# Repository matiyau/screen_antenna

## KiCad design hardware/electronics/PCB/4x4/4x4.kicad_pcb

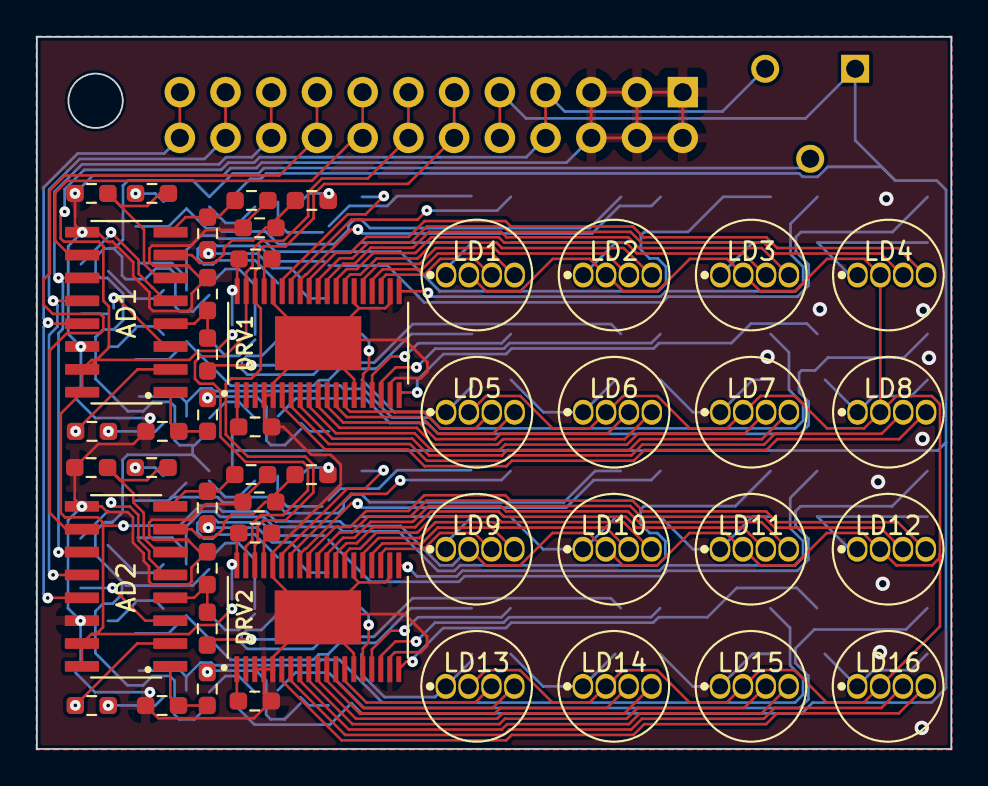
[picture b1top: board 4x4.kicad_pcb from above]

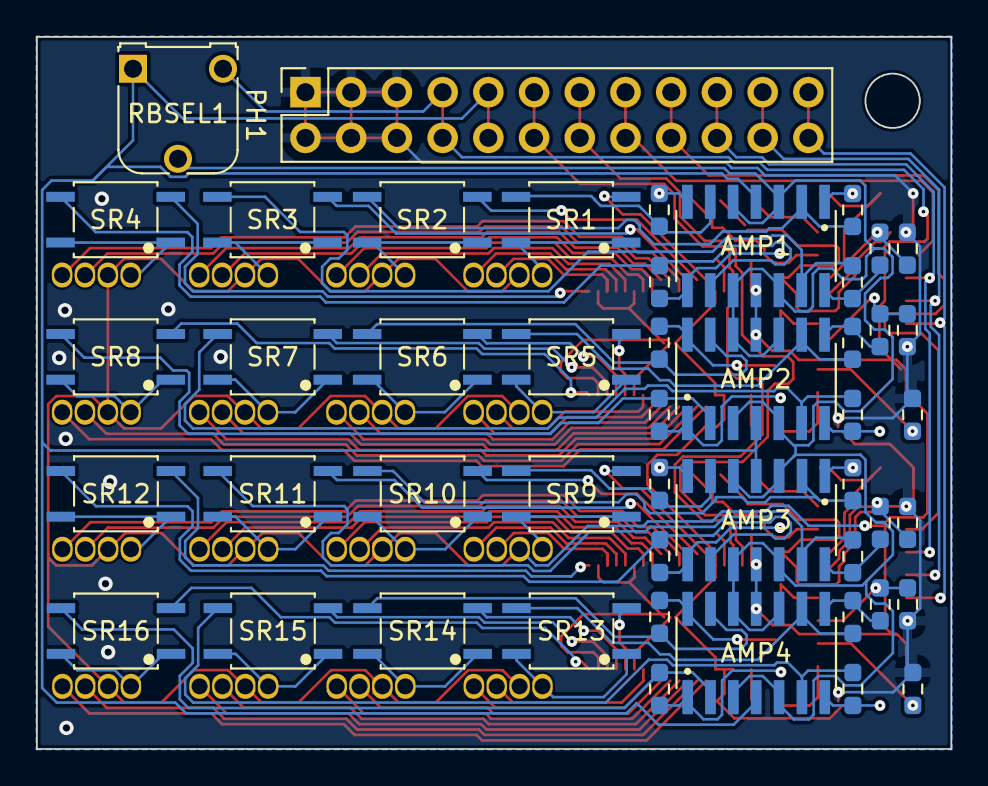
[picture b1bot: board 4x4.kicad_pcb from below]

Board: 2 copper layers, 50.8 x 39.6 mm, 94 parts (48 on the bottom side), 127 nets.

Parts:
AD1, AD2: MCP3008-I/P-DIP16; footprints_smd
AMP1, AMP2, AMP3, AMP4: MCP619-I/SL; footprints
DIV1, DIV2, DIV3, DIV4, DIV5, DIV6, DIV7, DIV8, DIV9, DIV10, DIV11, DIV12, DIV13, DIV14, DIV15, DIV16, DIV17, DIV18, DIV19, DIV20, DIV21, DIV22, DIV23, DIV24, DIV25, DIV26, DIV27, DIV28, DIV29, DIV30, DIV31, DIV32: 2K; Resistor - SMD - 1608Metric
DRV1, DRV2: PCA9956BTWY; SOP50P640X110-39N
FDB1, FDB2, FDB3, FDB4, FDB5, FDB6, FDB7, FDB8, FDB9, FDB10, FDB11, FDB12, FDB13, FDB14, FDB15, FDB16: 2M; Resistor - SMD - 1608Metric
ISEL1, ISEL2: 2K; Resistor - SMD - 1608Metric
LD1, LD2, LD3, LD4, LD5, LD6, LD7, LD8, LD9, LD10, LD11, LD12, LD13, LD14, LD15, LD16: WP154A4SEJ3VBDZGC/CA; WP154A4SEJ3VBDZGC&slash_CA
PH1: Conn_02x12_Odd_Even; PinSocket_2x12_P2.54mm_Vertical
PU1, PU2: 10K; Resistor - SMD - 1608Metric
RBSEL1: 100K; Potentiometer_Runtron_RM-065_Vertical
SR1, SR2, SR3, SR4, SR5, SR6, SR7, SR8, SR9, SR10, SR11, SR12, SR13, SR14, SR15, SR16: TLP4176ATP_F; footprints

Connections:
+5V: AD1.15 (VREF), AD1.16 (VDD), AD2.15 (VREF), AD2.16 (VDD), AMP1.11 (VSS), AMP2.11 (VSS), AMP3.11 (VSS), AMP4.11 (VSS), DRV1.38 (VDD), DRV2.38 (VDD), LD1.2 (CA), LD2.2 (CA), LD3.2 (CA), LD4.2 (CA), LD5.2 (CA), LD6.2 (CA), LD7.2 (CA), LD8.2 (CA), LD9.2 (CA), LD10.2 (CA), LD11.2 (CA), LD12.2 (CA), LD13.2 (CA), LD14.2 (CA), LD15.2 (CA), LD16.2 (CA), PH1.7, PH1.8, PU1.1, PU2.1, RBSEL1.3
+9V: AMP1.4 (VDD), AMP2.4 (VDD), AMP3.4 (VDD), AMP4.4 (VDD), PH1.9, PH1.10, RBSEL1.1
/LED 4x2 Bottom/ LDRow_Amps1/Amp_IP_1: AMP3.2 (VINA-), FDB9.2, SR10.3 (Load)
/LED 4x2 Bottom/ LDRow_Amps1/Amp_IP_2: AMP3.6 (VINB-), FDB10.2, SR9.3 (Load)
/LED 4x2 Bottom/ LDRow_Amps1/Amp_IP_3: AMP3.9 (VINC-), FDB11.2, SR12.3 (Load)
/LED 4x2 Bottom/ LDRow_Amps1/Amp_IP_4: AMP3.13 (VIND-), FDB12.2, SR11.3 (Load)
/LED 4x2 Bottom/ LDRow_Amps1/Amp_IP_5: AMP4.2 (VINA-), FDB13.2, SR16.3 (Load)
/LED 4x2 Bottom/ LDRow_Amps1/Amp_IP_6: AMP4.6 (VINB-), FDB14.2, SR15.3 (Load)
/LED 4x2 Bottom/ LDRow_Amps1/Amp_IP_7: AMP4.9 (VINC-), FDB15.2, SR13.3 (Load)
/LED 4x2 Bottom/ LDRow_Amps1/Amp_IP_8: AMP4.13 (VIND-), FDB16.2, SR14.3 (Load)
/LED 4x2 Bottom/ LDRow_Amps1/Amp_OP_1: AMP3.1 (VOUTA), DIV19.2, FDB9.1
/LED 4x2 Bottom/ LDRow_Amps1/Amp_OP_2: AMP3.7 (VOUTB), DIV17.2, FDB10.1
/LED 4x2 Bottom/ LDRow_Amps1/Amp_OP_3: AMP3.8 (VOUTC), DIV23.2, FDB11.1
/LED 4x2 Bottom/ LDRow_Amps1/Amp_OP_4: AMP3.14 (VOUTD), DIV21.2, FDB12.1
/LED 4x2 Bottom/ LDRow_Amps1/Amp_OP_5: AMP4.1 (VOUTA), DIV31.2, FDB13.1
/LED 4x2 Bottom/ LDRow_Amps1/Amp_OP_6: AMP4.7 (VOUTB), DIV29.2, FDB14.1
/LED 4x2 Bottom/ LDRow_Amps1/Amp_OP_7: AMP4.8 (VOUTC), DIV25.2, FDB15.1
/LED 4x2 Bottom/ LDRow_Amps1/Amp_OP_8: AMP4.14 (VOUTD), DIV27.2, FDB16.1
/LED 4x2 Bottom/LD1_B: DRV2.22 (LED13), LD9.3 (B)
/LED 4x2 Bottom/LD1_G: DRV2.23 (LED14), LD9.4 (G)
/LED 4x2 Bottom/LD1_R: LD9.1 (R), SR9.1 (+Ctr), SR9.4 (Load)
/LED 4x2 Bottom/LD2_B: DRV2.24 (LED15), LD10.3 (B)
/LED 4x2 Bottom/LD2_G: DRV2.26 (LED16), LD10.4 (G)
/LED 4x2 Bottom/LD2_R: LD10.1 (R), SR10.1 (+Ctr), SR10.4 (Load)
/LED 4x2 Bottom/LD3_B: DRV2.27 (LED17), LD11.3 (B)
/LED 4x2 Bottom/LD3_G: DRV2.28 (LED18), LD11.4 (G)
/LED 4x2 Bottom/LD3_R: LD11.1 (R), SR11.1 (+Ctr), SR11.4 (Load)
/LED 4x2 Bottom/LD4_B: DRV2.29 (LED19), LD12.3 (B)
/LED 4x2 Bottom/LD4_G: DRV2.30 (LED20), LD12.4 (G)
/LED 4x2 Bottom/LD4_R: LD12.1 (R), SR12.1 (+Ctr), SR12.4 (Load)
/LED 4x2 Bottom/LD5_B: DRV2.13 (LED7), LD13.3 (B)
/LED 4x2 Bottom/LD5_G: DRV2.12 (LED6), LD13.4 (G)
/LED 4x2 Bottom/LD5_R: LD13.1 (R), SR13.1 (+Ctr), SR13.4 (Load)
/LED 4x2 Bottom/LD6_B: DRV2.11 (LED5), LD14.3 (B)
/LED 4x2 Bottom/LD6_G: DRV2.10 (LED4), LD14.4 (G)
/LED 4x2 Bottom/LD6_R: LD14.1 (R), SR14.1 (+Ctr), SR14.4 (Load)
/LED 4x2 Bottom/LD7_B: DRV2.9 (LED3), LD15.3 (B)
/LED 4x2 Bottom/LD7_G: DRV2.8 (LED2), LD15.4 (G)
/LED 4x2 Bottom/LD7_R: LD15.1 (R), SR15.1 (+Ctr), SR15.4 (Load)
/LED 4x2 Bottom/LD8_B: DRV2.7 (LED1), LD16.3 (B)
/LED 4x2 Bottom/LD8_G: DRV2.6 (LED0), LD16.4 (G)
/LED 4x2 Bottom/LD8_R: LD16.1 (R), SR16.1 (+Ctr), SR16.4 (Load)
/LED 4x2 Bottom/SR1_R: DRV2.33 (LED23), SR9.2 (-Ctr)
/LED 4x2 Bottom/SR2_R: DRV2.32 (LED22), SR10.2 (-Ctr)
/LED 4x2 Bottom/SR3_R: DRV2.31 (LED21), SR11.2 (-Ctr)
/LED 4x2 Bottom/SR4_R: DRV2.20 (LED12), SR12.2 (-Ctr)
/LED 4x2 Bottom/SR5_R: DRV2.15 (LED8), SR13.2 (-Ctr)
/LED 4x2 Bottom/SR6_R: DRV2.16 (LED9), SR14.2 (-Ctr)
/LED 4x2 Bottom/SR7_R: DRV2.17 (LED10), SR15.2 (-Ctr)
/LED 4x2 Bottom/SR8_R: DRV2.19 (LED11), SR16.2 (-Ctr)
/LED 4x2 Top/ LDRow_Amps1/Amp_IP_1: AMP1.2 (VINA-), FDB1.2, SR2.3 (Load)
/LED 4x2 Top/ LDRow_Amps1/Amp_IP_2: AMP1.6 (VINB-), FDB2.2, SR1.3 (Load)
/LED 4x2 Top/ LDRow_Amps1/Amp_IP_3: AMP1.9 (VINC-), FDB3.2, SR4.3 (Load)
/LED 4x2 Top/ LDRow_Amps1/Amp_IP_4: AMP1.13 (VIND-), FDB4.2, SR3.3 (Load)
/LED 4x2 Top/ LDRow_Amps1/Amp_IP_5: AMP2.2 (VINA-), FDB5.2, SR8.3 (Load)
/LED 4x2 Top/ LDRow_Amps1/Amp_IP_6: AMP2.6 (VINB-), FDB6.2, SR7.3 (Load)
/LED 4x2 Top/ LDRow_Amps1/Amp_IP_7: AMP2.9 (VINC-), FDB7.2, SR5.3 (Load)
/LED 4x2 Top/ LDRow_Amps1/Amp_IP_8: AMP2.13 (VIND-), FDB8.2, SR6.3 (Load)
/LED 4x2 Top/ LDRow_Amps1/Amp_OP_1: AMP1.1 (VOUTA), DIV3.2, FDB1.1
/LED 4x2 Top/ LDRow_Amps1/Amp_OP_2: AMP1.7 (VOUTB), DIV1.2, FDB2.1
/LED 4x2 Top/ LDRow_Amps1/Amp_OP_3: AMP1.8 (VOUTC), DIV7.2, FDB3.1
/LED 4x2 Top/ LDRow_Amps1/Amp_OP_4: AMP1.14 (VOUTD), DIV5.2, FDB4.1
/LED 4x2 Top/ LDRow_Amps1/Amp_OP_5: AMP2.1 (VOUTA), DIV15.2, FDB5.1
/LED 4x2 Top/ LDRow_Amps1/Amp_OP_6: AMP2.7 (VOUTB), DIV13.2, FDB6.1
/LED 4x2 Top/ LDRow_Amps1/Amp_OP_7: AMP2.8 (VOUTC), DIV9.2, FDB7.1
/LED 4x2 Top/ LDRow_Amps1/Amp_OP_8: AMP2.14 (VOUTD), DIV11.2, FDB8.1
/LED 4x2 Top/LD1_B: DRV1.22 (LED13), LD1.3 (B)
/LED 4x2 Top/LD1_G: DRV1.23 (LED14), LD1.4 (G)
/LED 4x2 Top/LD1_R: LD1.1 (R), SR1.1 (+Ctr), SR1.4 (Load)
/LED 4x2 Top/LD2_B: DRV1.24 (LED15), LD2.3 (B)
/LED 4x2 Top/LD2_G: DRV1.26 (LED16), LD2.4 (G)
/LED 4x2 Top/LD2_R: LD2.1 (R), SR2.1 (+Ctr), SR2.4 (Load)
/LED 4x2 Top/LD3_B: DRV1.27 (LED17), LD3.3 (B)
/LED 4x2 Top/LD3_G: DRV1.28 (LED18), LD3.4 (G)
/LED 4x2 Top/LD3_R: LD3.1 (R), SR3.1 (+Ctr), SR3.4 (Load)
/LED 4x2 Top/LD4_B: DRV1.29 (LED19), LD4.3 (B)
/LED 4x2 Top/LD4_G: DRV1.30 (LED20), LD4.4 (G)
/LED 4x2 Top/LD4_R: LD4.1 (R), SR4.1 (+Ctr), SR4.4 (Load)
/LED 4x2 Top/LD5_B: DRV1.13 (LED7), LD5.3 (B)
/LED 4x2 Top/LD5_G: DRV1.12 (LED6), LD5.4 (G)
/LED 4x2 Top/LD5_R: LD5.1 (R), SR5.1 (+Ctr), SR5.4 (Load)
/LED 4x2 Top/LD6_B: DRV1.11 (LED5), LD6.3 (B)
/LED 4x2 Top/LD6_G: DRV1.10 (LED4), LD6.4 (G)
/LED 4x2 Top/LD6_R: LD6.1 (R), SR6.1 (+Ctr), SR6.4 (Load)
/LED 4x2 Top/LD7_B: DRV1.9 (LED3), LD7.3 (B)
/LED 4x2 Top/LD7_G: DRV1.8 (LED2), LD7.4 (G)
/LED 4x2 Top/LD7_R: LD7.1 (R), SR7.1 (+Ctr), SR7.4 (Load)
/LED 4x2 Top/LD8_B: DRV1.7 (LED1), LD8.3 (B)
/LED 4x2 Top/LD8_G: DRV1.6 (LED0), LD8.4 (G)
/LED 4x2 Top/LD8_R: LD8.1 (R), SR8.1 (+Ctr), SR8.4 (Load)
/LED 4x2 Top/SR1_R: DRV1.33 (LED23), SR1.2 (-Ctr)
/LED 4x2 Top/SR2_R: DRV1.32 (LED22), SR2.2 (-Ctr)
/LED 4x2 Top/SR3_R: DRV1.31 (LED21), SR3.2 (-Ctr)
/LED 4x2 Top/SR4_R: DRV1.20 (LED12), SR4.2 (-Ctr)
/LED 4x2 Top/SR5_R: DRV1.15 (LED8), SR5.2 (-Ctr)
/LED 4x2 Top/SR6_R: DRV1.16 (LED9), SR6.2 (-Ctr)
/LED 4x2 Top/SR7_R: DRV1.17 (LED10), SR7.2 (-Ctr)
/LED 4x2 Top/SR8_R: DRV1.19 (LED11), SR8.2 (-Ctr)
GND: AD1.9 (DGND), AD1.14 (AGND), AD2.9 (DGND), AD2.14 (AGND), DIV2.1, DIV4.1, DIV6.1, DIV8.1, DIV10.1, DIV12.1, DIV14.1, DIV16.1, DIV18.1, DIV20.1, DIV22.1, DIV24.1, DIV26.1, DIV28.1, DIV30.1, DIV32.1, DRV1.4 (AD2), DRV1.5 (~OE), DRV1.14 (VSS), DRV1.18 (VSS), DRV1.21 (VSS), DRV1.25 (VSS), DRV1.34 (VSS), DRV1.39 (EXP), DRV2.3 (AD1), DRV2.4 (AD2), DRV2.5 (~OE), DRV2.14 (VSS), DRV2.18 (VSS), DRV2.21 (VSS), DRV2.25 (VSS), DRV2.34 (VSS), DRV2.39 (EXP), ISEL1.1, ISEL2.1, PH1.1, PH1.2, PH1.3, PH1.4, PH1.5, PH1.6
I2C_SCL: DRV1.36 (SCL), DRV2.36 (SCL), PH1.11, PH1.12
I2C_SDA: DRV1.37 (SDA), DRV2.37 (SDA), PH1.13, PH1.14
unnamed: AD1.1 (CH0), DIV15.1, DIV16.2
unnamed: AD1.2 (CH1), DIV13.1, DIV14.2
unnamed: AD1.3 (CH2), DIV9.1, DIV10.2
unnamed: AD1.4 (CH3), DIV11.1, DIV12.2
unnamed: AD1.5 (CH4), DIV5.1, DIV6.2
unnamed: AD1.6 (CH5), DIV3.1, DIV4.2
unnamed: AD1.7 (CH6), DIV1.1, DIV2.2
unnamed: AD1.8 (CH7), DIV7.1, DIV8.2
unnamed: AD2.1 (CH0), DIV31.1, DIV32.2
unnamed: AD2.2 (CH1), DIV29.1, DIV30.2
unnamed: AD2.3 (CH2), DIV25.1, DIV26.2
unnamed: AD2.4 (CH3), DIV27.1, DIV28.2
unnamed: AD2.5 (CH4), DIV21.1, DIV22.2
unnamed: AD2.6 (CH5), DIV19.1, DIV20.2
unnamed: AD2.7 (CH6), DIV17.1, DIV18.2
unnamed: AD2.8 (CH7), DIV23.1, DIV24.2
unnamed: DRV1.1 (REXT), ISEL1.2
unnamed: DRV1.35 (~RESET), PU1.2
unnamed: DRV2.1 (REXT), ISEL2.2
unnamed: DRV2.35 (~RESET), PU2.2
RB Voltage: AMP1.3 (VINA+), AMP1.5 (VINB+), AMP1.10 (VINC+), AMP1.12 (VIND+), AMP2.3 (VINA+), AMP2.5 (VINB+), AMP2.10 (VINC+), AMP2.12 (VIND+), AMP3.3 (VINA+), AMP3.5 (VINB+), AMP3.10 (VINC+), AMP3.12 (VIND+), AMP4.3 (VINA+), AMP4.5 (VINB+), AMP4.10 (VINC+), AMP4.12 (VIND+), RBSEL1.2
SPI_MISO: AD1.12 (DOUT), AD2.12 (DOUT), PH1.21, PH1.22
SPI_MOSI: AD1.11 (DIN), AD2.11 (DIN), PH1.19, PH1.20
SPI_SCK: AD1.13 (CLK), AD2.13 (CLK), PH1.23, PH1.24
SPI_SS_0: AD1.10 (SHDN/~CS), PH1.15, PH1.16
SPI_SS_1: AD2.10 (SHDN/~CS), PH1.17, PH1.18

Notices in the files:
parts and their libraries:
Copyright 2021 Accelerated Designs. All rights reserved.
